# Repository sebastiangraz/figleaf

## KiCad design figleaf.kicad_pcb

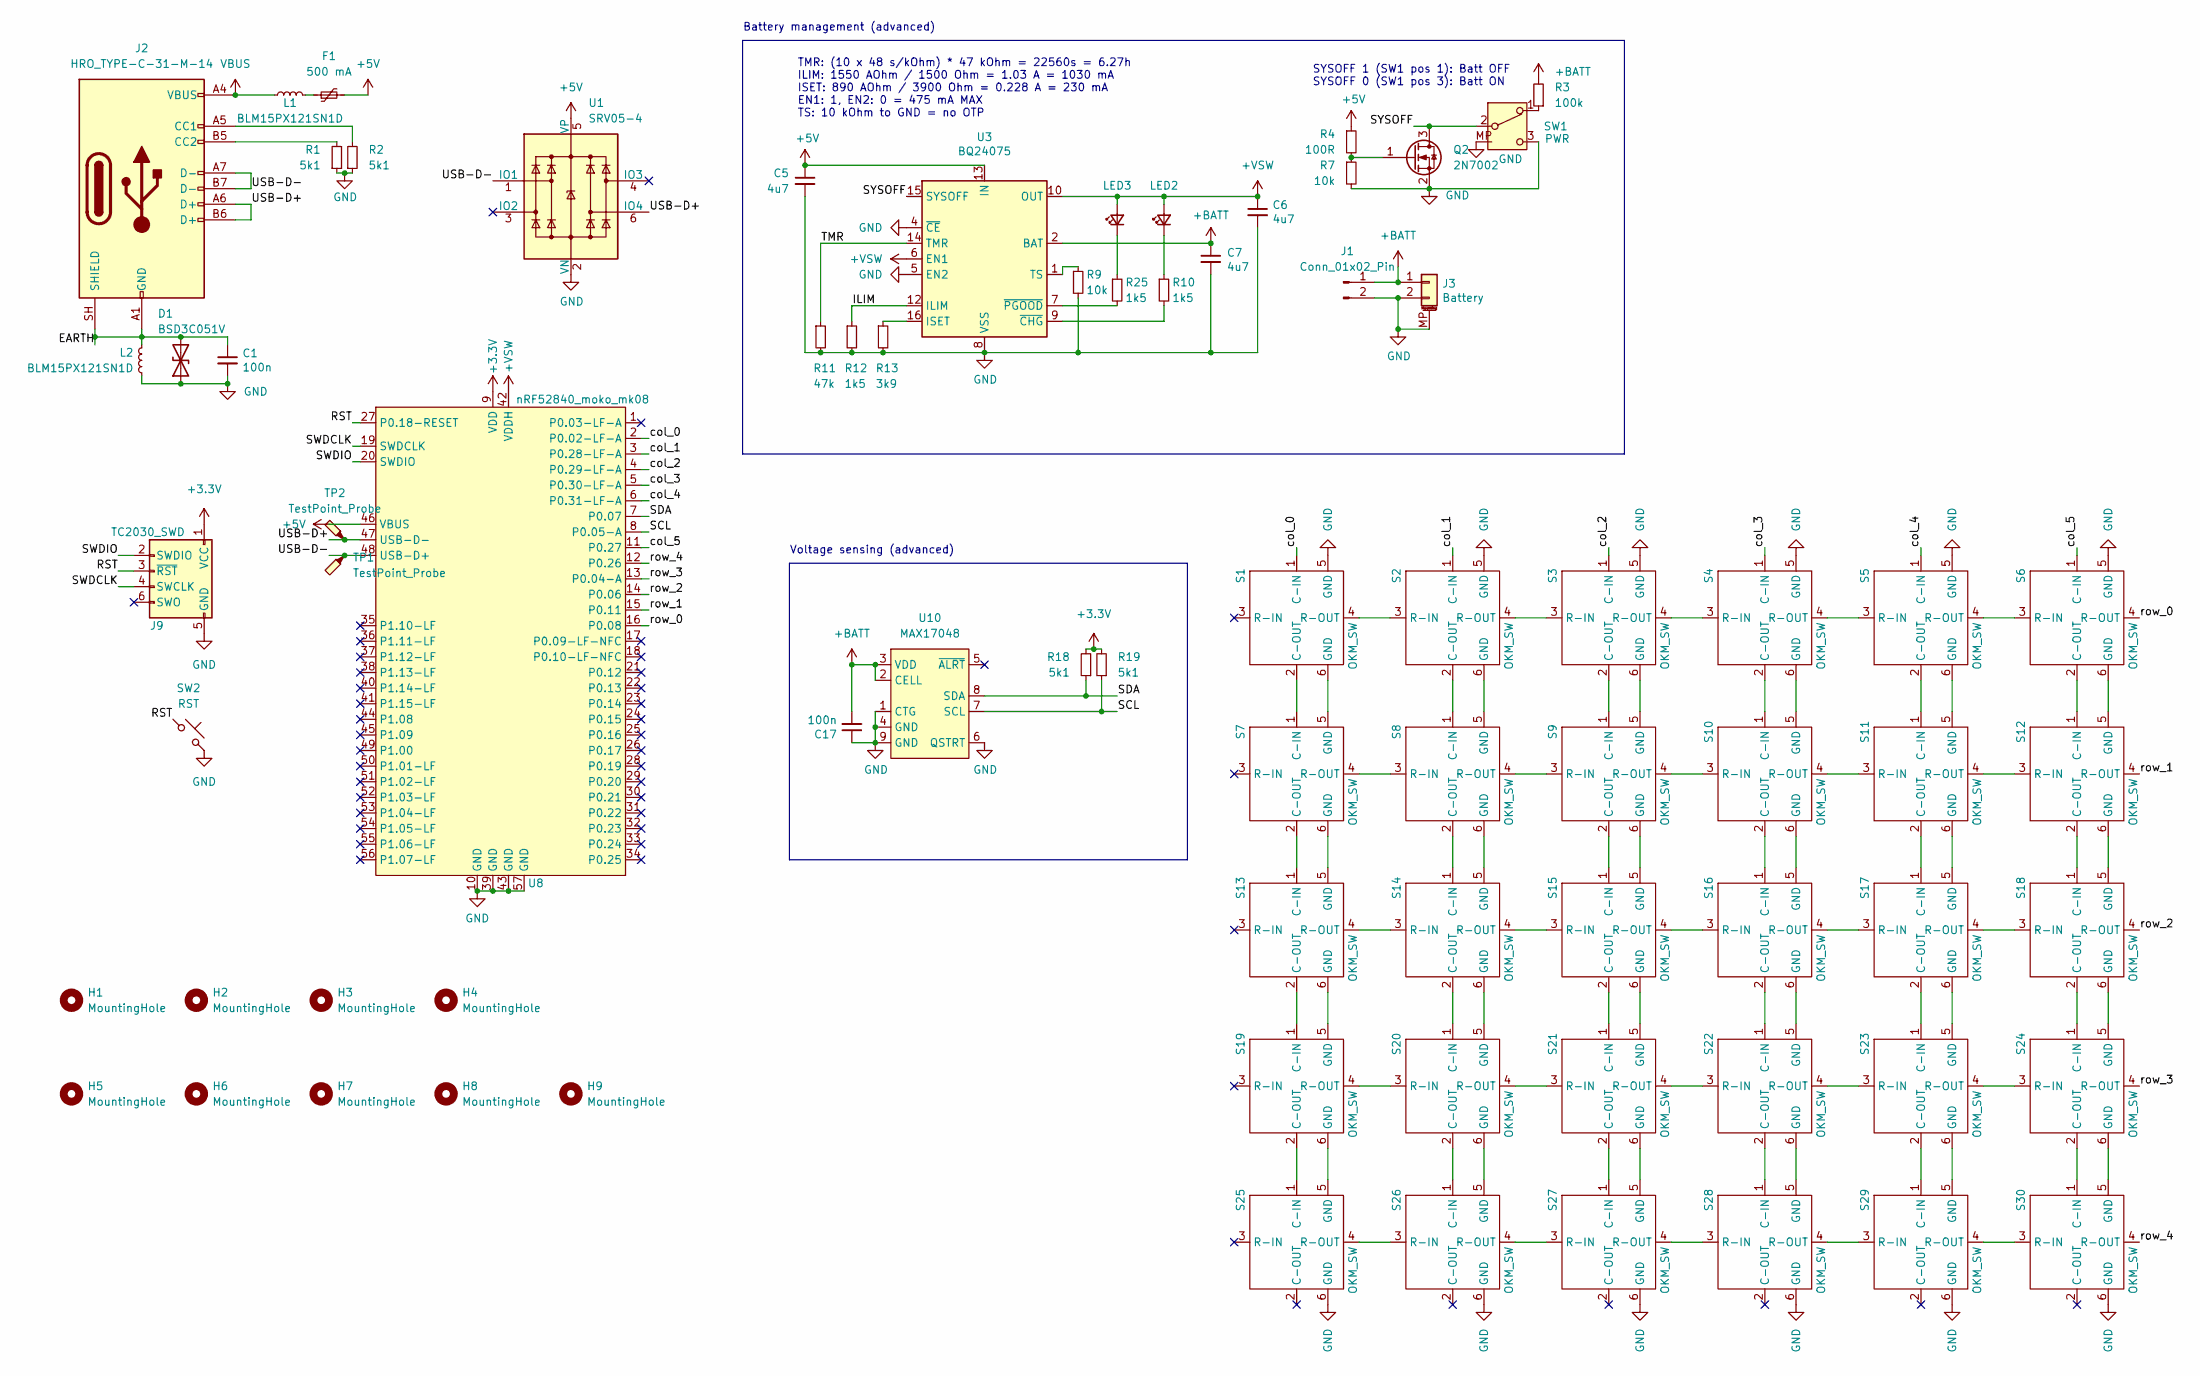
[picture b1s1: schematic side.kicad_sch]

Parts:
C1, C17: 100n; C_0402_1005Metric
C5, C6, C7: 4u7; C_0402_1005Metric
D1: BSD3C051V; D_SOD-323
F1: 500 mA; Fuse_1206_3216Metric
H1, H2, H3, H4, H5, H6, H7, H8, H9: MountingHole; MHOLE_M2
J1: Conn_01x02_Pin; BATT_CONN_SMD
J2: HRO_TYPE-C-31-M-14; USB_C_Receptacle_HRO_TYPE-C-31-M-14
J3: Battery; JST_SH_SM02B-SRSS-TB_1x02-1MP_P1.00mm_Horizontal; LCSC C505023
J9: TC2030_SWD; CON_TC2030_outlined
L1, L2: BLM15PX121SN1D; L_0402_1005Metric
LED2: LW QH8G-Q2OO-3K5L-1; LED_0402_1005Metric
LED3: LT VH9G-Q2OO-25-1; LED_0402_1005Metric
Q2: 2N7002; SOT-23
R1, R2, R18, R19: 5k1; R_0402_1005Metric
R3: 100k; R_0402_1005Metric
R4: 100R; R_0402_1005Metric
R7, R9: 10k; R_0402_1005Metric
R10, R12, R25: 1k5; R_0402_1005Metric
R11: 47k; R_0402_1005Metric
R13: 3k9; R_0402_1005Metric
S1, S2, S3, S4, S5, S6, S7, S8, S9, S10, S11, S12, S13, S14, S15, S16, S17, S18, S19, S20, S21, S22, S23, S24, S25, S26, S27, S28, S29, S30: OKM_SW
SW1: PWR; ALPS_SPDT_SW
SW2: RST; SW_SPST_B3U-3000P-B
TP1, TP2: TestPoint_Probe; TestPoint_Pad_D1.0mm
U1: SRV05-4; SOT-23-6
U3: BQ24075; VQFN-16-1EP_3x3mm_P0.5mm_EP1.6x1.6mm
U8: nRF52840_moko_mk08; MOKO_MK08
U10: MAX17048; DFN-8-1EP_2x2mm_P0.5mm_EP0.7x1.3mm_SM0.22mm

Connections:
+3.3V: J9.1 (VCC), R18.2, R19.2, U8.9 (VDD); also elsewhere on the board
+5V: C5.1, F1.2, R4.1, U1.5 (VP), U3.13 (IN), U8.46 (VBUS); also elsewhere on the board
+BATT: C7.1, C17.2, J1.1, J3.1, R3.2, U3.2 (BAT), U3.3 (BAT), U10.2 (CELL), U10.3 (VDD); also elsewhere on the board
+VSW: C6.1, LED2.2 (A), LED3.2 (A), U3.6 (EN1), U3.10 (OUT), U3.11 (OUT), U8.42 (VDDH); also elsewhere on the board
/left/EARTH: C1.1, D1.2 (A2), J2.A1 (GND), J2.A12 (GND), J2.B1 (GND), J2.B12 (GND), J2.SH (SHIELD), L2.1
/left/ILIM: R12.1, U3.12 (ILIM)
/left/RST: J9.3 (~RST), SW2.1, U8.27 (P0.18-RESET)
/left/SCL: R19.1, U8.8 (P0.05-A), U10.7 (SCL)
/left/SDA: R18.1, U8.7 (P0.07), U10.8 (SDA)
/left/SWDCLK: J9.4 (SWCLK), U8.19 (SWDCLK)
/left/SWDIO: J9.2 (SWDIO), U8.20 (SWDIO)
/left/SYSOFF: Q2.3 (D), SW1.2 (B), U3.15 (SYSOFF)
/left/TMR: R11.1, U3.14 (TMR)
/left/USB-D+: J2.A6 (D+), J2.B6 (D+), TP2.1 (1_1), U1.6 (IO4), U8.47 (USB-D-)
/left/USB-D-: J2.A7 (D-), J2.B7 (D-), TP1.1 (1_1), U1.1 (IO1), U8.48 (USB-D+)
/left/col_0: S1.1 (C-IN), U8.2 (P0.02-LF-A)
/left/col_1: S2.1 (C-IN), U8.3 (P0.28-LF-A)
/left/col_2: S3.1 (C-IN), U8.4 (P0.29-LF-A)
/left/col_3: S4.1 (C-IN), U8.5 (P0.30-LF-A)
/left/col_4: S5.1 (C-IN), U8.6 (P0.31-LF-A)
/left/col_5: S6.1 (C-IN), U8.11 (P0.27)
/left/row_0: S6.4 (R-OUT), U8.16 (P0.08)
/left/row_1: S12.4 (R-OUT), U8.15 (P0.11)
/left/row_2: S18.4 (R-OUT), U8.14 (P0.06)
/left/row_3: S24.4 (R-OUT), U8.13 (P0.04-A)
/left/row_4: S30.4 (R-OUT), U8.12 (P0.26)
GND: C1.2, C5.2, C6.2, C7.2, C17.1, D1.1 (A1), J1.2, J3.2, J3.MP (MountPin), J9.5 (GND), L2.2, Q2.2 (S), R1.1, R2.1, R7.2, R9.2, R11.2, R12.2, R13.2, S1.5 (GND), S2.5 (GND), S3.5 (GND), S4.5 (GND), S5.5 (GND), S6.5 (GND), S25.6 (GND), S26.6 (GND), S27.6 (GND), S28.6 (GND), S29.6 (GND), S30.6 (GND), SW1.3 (C), SW1.MP, SW2.2, U1.2 (VN), U3.4 (~CE), U3.5 (EN2), U3.8 (VSS), U3.17 (VSS), U8.10 (GND), U8.39 (GND), U8.43 (GND), U8.57 (GND), U10.1 (CTG), U10.4 (GND), U10.6 (QSTRT), U10.9 (GND); also elsewhere on the board
unnamed: F1.1, L1.2
unnamed: J2.A5 (CC1), R2.2
unnamed: J2.B5 (CC2), R1.2
unnamed: LED2.1 (K), R10.1
unnamed: LED3.1 (K), R25.1
unnamed: Q2.1 (G), R4.2, R7.1
unnamed: S1.2 (C-OUT), S7.1 (C-IN)
unnamed: S1.6 (GND), S7.5 (GND)
unnamed: S1.4 (R-OUT), S2.3 (R-IN)
unnamed: S2.2 (C-OUT), S8.1 (C-IN)
unnamed: S2.6 (GND), S8.5 (GND)
unnamed: S2.4 (R-OUT), S3.3 (R-IN)
unnamed: S3.2 (C-OUT), S9.1 (C-IN)
unnamed: S3.6 (GND), S9.5 (GND)
unnamed: S3.4 (R-OUT), S4.3 (R-IN)
unnamed: S4.4 (R-OUT), S5.3 (R-IN)
unnamed: S5.4 (R-OUT), S6.3 (R-IN)
unnamed: S7.4 (R-OUT), S8.3 (R-IN)
unnamed: S8.4 (R-OUT), S9.3 (R-IN)
unnamed: S4.2 (C-OUT), S10.1 (C-IN)
unnamed: S10.2 (C-OUT), S16.1 (C-IN)
unnamed: S4.6 (GND), S10.5 (GND)
unnamed: S10.6 (GND), S16.5 (GND)
unnamed: S9.4 (R-OUT), S10.3 (R-IN)
unnamed: S10.4 (R-OUT), S11.3 (R-IN)
unnamed: S5.2 (C-OUT), S11.1 (C-IN)
unnamed: S11.2 (C-OUT), S17.1 (C-IN)
unnamed: S5.6 (GND), S11.5 (GND)
unnamed: S11.6 (GND), S17.5 (GND)
unnamed: S11.4 (R-OUT), S12.3 (R-IN)
unnamed: S6.2 (C-OUT), S12.1 (C-IN)
unnamed: S12.2 (C-OUT), S18.1 (C-IN)
unnamed: S6.6 (GND), S12.5 (GND)
unnamed: S12.6 (GND), S18.5 (GND)
unnamed: S7.2 (C-OUT), S13.1 (C-IN)
unnamed: S13.2 (C-OUT), S19.1 (C-IN)
unnamed: S7.6 (GND), S13.5 (GND)
unnamed: S13.6 (GND), S19.5 (GND)
unnamed: S13.4 (R-OUT), S14.3 (R-IN)
unnamed: S8.2 (C-OUT), S14.1 (C-IN)
unnamed: S14.2 (C-OUT), S20.1 (C-IN)
unnamed: S8.6 (GND), S14.5 (GND)
unnamed: S14.6 (GND), S20.5 (GND)
unnamed: S14.4 (R-OUT), S15.3 (R-IN)
unnamed: S9.2 (C-OUT), S15.1 (C-IN)
unnamed: S15.2 (C-OUT), S21.1 (C-IN)
unnamed: S9.6 (GND), S15.5 (GND)
unnamed: S15.6 (GND), S21.5 (GND)
unnamed: S15.4 (R-OUT), S16.3 (R-IN)
unnamed: S16.2 (C-OUT), S22.1 (C-IN)
unnamed: S16.6 (GND), S22.5 (GND)
unnamed: S16.4 (R-OUT), S17.3 (R-IN)
unnamed: S17.2 (C-OUT), S23.1 (C-IN)
unnamed: S17.6 (GND), S23.5 (GND)
unnamed: S17.4 (R-OUT), S18.3 (R-IN)
unnamed: S18.2 (C-OUT), S24.1 (C-IN)
unnamed: S18.6 (GND), S24.5 (GND)
unnamed: S19.2 (C-OUT), S25.1 (C-IN)
unnamed: S19.6 (GND), S25.5 (GND)
unnamed: S19.4 (R-OUT), S20.3 (R-IN)
unnamed: S20.2 (C-OUT), S26.1 (C-IN)
unnamed: S20.6 (GND), S26.5 (GND)
unnamed: S20.4 (R-OUT), S21.3 (R-IN)
unnamed: S21.2 (C-OUT), S27.1 (C-IN)
unnamed: S21.6 (GND), S27.5 (GND)
unnamed: S21.4 (R-OUT), S22.3 (R-IN)
unnamed: S22.2 (C-OUT), S28.1 (C-IN)
unnamed: S22.6 (GND), S28.5 (GND)
unnamed: S22.4 (R-OUT), S23.3 (R-IN)
unnamed: S23.2 (C-OUT), S29.1 (C-IN)
unnamed: S23.6 (GND), S29.5 (GND)
unnamed: S23.4 (R-OUT), S24.3 (R-IN)
unnamed: S24.2 (C-OUT), S30.1 (C-IN)
unnamed: S24.6 (GND), S30.5 (GND)
unnamed: S25.4 (R-OUT), S26.3 (R-IN)
unnamed: S26.4 (R-OUT), S27.3 (R-IN)
unnamed: S27.4 (R-OUT), S28.3 (R-IN)
unnamed: S28.4 (R-OUT), S29.3 (R-IN)
unnamed: S29.4 (R-OUT), S30.3 (R-IN)
unnamed: R3.1, SW1.1 (A)
unnamed: R13.1, U3.16 (ISET)
unnamed: R9.1, U3.1 (TS)
unnamed: R10.2, U3.9 (~CHG)
unnamed: R25.2, U3.7 (~PGOOD)
VBUS: J2.A4 (VBUS), J2.A9 (VBUS), J2.B4 (VBUS), J2.B9 (VBUS), L1.1; also elsewhere on the board

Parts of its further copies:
C2, C3, C4: 4u7; C_0402_1005Metric
C8, C9: 100n; C_0402_1005Metric
D2: BSD3C051V; D_SOD-323
F2: 500 mA; Fuse_1206_3216Metric
H10, H11, H12, H13, H14, H15, H16, H17, H18: MountingHole; MHOLE_M2
J4: HRO_TYPE-C-31-M-14; USB_C_Receptacle_HRO_TYPE-C-31-M-14
J5: Conn_01x02_Pin; BATT_CONN_SMD
J6: Battery; JST_SH_SM02B-SRSS-TB_1x02-1MP_P1.00mm_Horizontal; LCSC C505023
J7: TC2030_SWD; CON_TC2030_outlined
L3, L4: BLM15PX121SN1D; L_0402_1005Metric
LED1: LW QH8G-Q2OO-3K5L-1; LED_0402_1005Metric
LED4: LT VH9G-Q2OO-25-1; LED_0402_1005Metric
Q1: 2N7002; SOT-23
R5: 100k; R_0402_1005Metric
R6: 100R; R_0402_1005Metric
R8, R14, R23, R24: 5k1; R_0402_1005Metric
R15, R16: 10k; R_0402_1005Metric
R17, R21, R26: 1k5; R_0402_1005Metric
R20: 47k; R_0402_1005Metric
R22: 3k9; R_0402_1005Metric
S31, S32, S33, S34, S35, S36, S37, S38, S39, S40, S41, S42, S43, S44, S45, S46, S47, S48, S49, S50, S51, S52, S53, S54, S55, S56, S57, S58, S59, S60: OKM_SW
SW3: PWR; ALPS_SPDT_SW
SW4: RST; SW_SPST_B3U-3000P-B
TP3, TP4: TestPoint_Probe; TestPoint_Pad_D1.0mm
U2: SRV05-4; SOT-23-6
U4: BQ24075; VQFN-16-1EP_3x3mm_P0.5mm_EP1.6x1.6mm
U5: nRF52840_moko_mk08; MOKO_MK08
U6: MAX17048; DFN-8-1EP_2x2mm_P0.5mm_EP0.7x1.3mm_SM0.22mm

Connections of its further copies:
+3.3V: J7.1 (VCC), R23.2, R24.2, U5.9 (VDD); also elsewhere on the board
+5V: C2.1, F2.2, R6.1, U2.5 (VP), U4.13 (IN), U5.46 (VBUS); also elsewhere on the board
+BATT: C4.1, C9.2, J5.1, J6.1, R5.2, U4.2 (BAT), U4.3 (BAT), U6.2 (CELL), U6.3 (VDD); also elsewhere on the board
+VSW: C3.1, LED1.2 (A), LED4.2 (A), U4.6 (EN1), U4.10 (OUT), U4.11 (OUT), U5.42 (VDDH); also elsewhere on the board
/right/EARTH: C8.1, D2.2 (A2), J4.A1 (GND), J4.A12 (GND), J4.B1 (GND), J4.B12 (GND), J4.SH (SHIELD), L4.1
/right/ILIM: R21.1, U4.12 (ILIM)
/right/RST: J7.3 (~RST), SW4.1, U5.27 (P0.18-RESET)
/right/SCL: R24.1, U5.8 (P0.05-A), U6.7 (SCL)
/right/SDA: R23.1, U5.7 (P0.07), U6.8 (SDA)
/right/SWDCLK: J7.4 (SWCLK), U5.19 (SWDCLK)
/right/SWDIO: J7.2 (SWDIO), U5.20 (SWDIO)
/right/SYSOFF: Q1.3 (D), SW3.2 (B), U4.15 (SYSOFF)
/right/TMR: R20.1, U4.14 (TMR)
/right/USB-D+: J4.A6 (D+), J4.B6 (D+), TP3.1 (1_1), U2.6 (IO4), U5.47 (USB-D-)
/right/USB-D-: J4.A7 (D-), J4.B7 (D-), TP4.1 (1_1), U2.1 (IO1), U5.48 (USB-D+)
/right/col_0: S31.1 (C-IN), U5.2 (P0.02-LF-A)
/right/col_1: S32.1 (C-IN), U5.3 (P0.28-LF-A)
/right/col_2: S33.1 (C-IN), U5.4 (P0.29-LF-A)
/right/col_3: S34.1 (C-IN), U5.5 (P0.30-LF-A)
/right/col_4: S35.1 (C-IN), U5.6 (P0.31-LF-A)
/right/col_5: S36.1 (C-IN), U5.11 (P0.27)
/right/row_0: S36.4 (R-OUT), U5.16 (P0.08)
/right/row_1: S42.4 (R-OUT), U5.15 (P0.11)
/right/row_2: S48.4 (R-OUT), U5.14 (P0.06)
/right/row_3: S54.4 (R-OUT), U5.13 (P0.04-A)
/right/row_4: S60.4 (R-OUT), U5.12 (P0.26)
GND: C2.2, C3.2, C4.2, C8.2, C9.1, D2.1 (A1), J5.2, J6.2, J6.MP (MountPin), J7.5 (GND), L4.2, Q1.2 (S), R8.1, R14.1, R15.2, R16.2, R20.2, R21.2, R22.2, S31.5 (GND), S32.5 (GND), S33.5 (GND), S34.5 (GND), S35.5 (GND), S36.5 (GND), S55.6 (GND), S56.6 (GND), S57.6 (GND), S58.6 (GND), S59.6 (GND), S60.6 (GND), SW3.3 (C), SW3.MP, SW4.2, U2.2 (VN), U4.4 (~CE), U4.5 (EN2), U4.8 (VSS), U4.17 (VSS), U5.10 (GND), U5.39 (GND), U5.43 (GND), U5.57 (GND), U6.1 (CTG), U6.4 (GND), U6.6 (QSTRT), U6.9 (GND); also elsewhere on the board
unnamed: F2.1, L3.2
unnamed: J4.A5 (CC1), R14.2
unnamed: J4.B5 (CC2), R8.2
unnamed: LED1.1 (K), R17.1
unnamed: LED4.1 (K), R26.1
unnamed: Q1.1 (G), R6.2, R15.1
unnamed: S31.2 (C-OUT), S37.1 (C-IN)
unnamed: S31.6 (GND), S37.5 (GND)
unnamed: S31.4 (R-OUT), S32.3 (R-IN)
unnamed: S32.2 (C-OUT), S38.1 (C-IN)
unnamed: S32.6 (GND), S38.5 (GND)
unnamed: S32.4 (R-OUT), S33.3 (R-IN)
unnamed: S33.2 (C-OUT), S39.1 (C-IN)
unnamed: S33.6 (GND), S39.5 (GND)
unnamed: S33.4 (R-OUT), S34.3 (R-IN)
unnamed: S34.2 (C-OUT), S40.1 (C-IN)
unnamed: S34.6 (GND), S40.5 (GND)
unnamed: S34.4 (R-OUT), S35.3 (R-IN)
unnamed: S35.2 (C-OUT), S41.1 (C-IN)
unnamed: S35.6 (GND), S41.5 (GND)
unnamed: S35.4 (R-OUT), S36.3 (R-IN)
unnamed: S36.2 (C-OUT), S42.1 (C-IN)
unnamed: S36.6 (GND), S42.5 (GND)
unnamed: S37.2 (C-OUT), S43.1 (C-IN)
unnamed: S37.6 (GND), S43.5 (GND)
unnamed: S37.4 (R-OUT), S38.3 (R-IN)
unnamed: S38.2 (C-OUT), S44.1 (C-IN)
unnamed: S38.6 (GND), S44.5 (GND)
unnamed: S38.4 (R-OUT), S39.3 (R-IN)
unnamed: S39.2 (C-OUT), S45.1 (C-IN)
unnamed: S39.6 (GND), S45.5 (GND)
unnamed: S39.4 (R-OUT), S40.3 (R-IN)
unnamed: S40.2 (C-OUT), S46.1 (C-IN)
unnamed: S40.6 (GND), S46.5 (GND)
unnamed: S40.4 (R-OUT), S41.3 (R-IN)
unnamed: S41.2 (C-OUT), S47.1 (C-IN)
unnamed: S41.6 (GND), S47.5 (GND)
unnamed: S41.4 (R-OUT), S42.3 (R-IN)
unnamed: S42.2 (C-OUT), S48.1 (C-IN)
unnamed: S42.6 (GND), S48.5 (GND)
unnamed: S43.2 (C-OUT), S49.1 (C-IN)
unnamed: S43.6 (GND), S49.5 (GND)
unnamed: S43.4 (R-OUT), S44.3 (R-IN)
unnamed: S44.2 (C-OUT), S50.1 (C-IN)
unnamed: S44.6 (GND), S50.5 (GND)
unnamed: S44.4 (R-OUT), S45.3 (R-IN)
unnamed: S45.2 (C-OUT), S51.1 (C-IN)
unnamed: S45.6 (GND), S51.5 (GND)
unnamed: S45.4 (R-OUT), S46.3 (R-IN)
unnamed: S46.2 (C-OUT), S52.1 (C-IN)
unnamed: S46.6 (GND), S52.5 (GND)
unnamed: S46.4 (R-OUT), S47.3 (R-IN)
unnamed: S47.2 (C-OUT), S53.1 (C-IN)
unnamed: S47.6 (GND), S53.5 (GND)
unnamed: S47.4 (R-OUT), S48.3 (R-IN)
unnamed: S48.2 (C-OUT), S54.1 (C-IN)
unnamed: S48.6 (GND), S54.5 (GND)
unnamed: S49.2 (C-OUT), S55.1 (C-IN)
unnamed: S49.6 (GND), S55.5 (GND)
unnamed: S49.4 (R-OUT), S50.3 (R-IN)
unnamed: S50.2 (C-OUT), S56.1 (C-IN)
unnamed: S50.6 (GND), S56.5 (GND)
unnamed: S50.4 (R-OUT), S51.3 (R-IN)
unnamed: S51.2 (C-OUT), S57.1 (C-IN)
unnamed: S51.6 (GND), S57.5 (GND)
unnamed: S51.4 (R-OUT), S52.3 (R-IN)
unnamed: S52.2 (C-OUT), S58.1 (C-IN)
unnamed: S52.6 (GND), S58.5 (GND)
unnamed: S52.4 (R-OUT), S53.3 (R-IN)
unnamed: S53.2 (C-OUT), S59.1 (C-IN)
unnamed: S53.6 (GND), S59.5 (GND)
unnamed: S53.4 (R-OUT), S54.3 (R-IN)
unnamed: S54.2 (C-OUT), S60.1 (C-IN)
unnamed: S54.6 (GND), S60.5 (GND)
unnamed: S55.4 (R-OUT), S56.3 (R-IN)
unnamed: S56.4 (R-OUT), S57.3 (R-IN)
unnamed: S57.4 (R-OUT), S58.3 (R-IN)
unnamed: S58.4 (R-OUT), S59.3 (R-IN)
unnamed: S59.4 (R-OUT), S60.3 (R-IN)
unnamed: R5.1, SW3.1 (A)
unnamed: R22.1, U4.16 (ISET)
unnamed: R16.1, U4.1 (TS)
unnamed: R17.2, U4.9 (~CHG)
unnamed: R26.2, U4.7 (~PGOOD)
VBUS: J4.A4 (VBUS), J4.A9 (VBUS), J4.B4 (VBUS), J4.B9 (VBUS), L3.1; also elsewhere on the board

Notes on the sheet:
SYSOFF 1 (SW1 pos 1): Batt OFF SYSOFF 0 (SW1 pos 3): Batt ON
TMR: (10 x 48 s/kOhm) * 47 kOhm = 22560s = 6.27h ILIM: 1550 AOhm / 1500 Ohm = 1.03 A = 1030 mA ISET: 890 AOhm / 3900 Ohm = 0.228 A = 230 mA EN1: 1, EN2: 0 = 475 mA MAX TS: 10 kOhm to GND = no OTP
Voltage sensing (advanced)
Battery management (advanced)

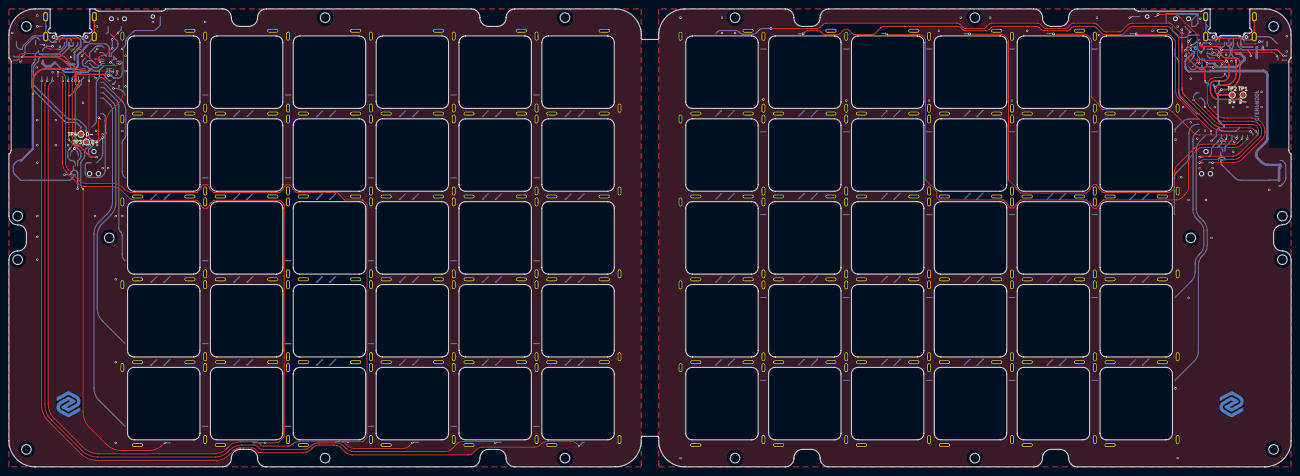
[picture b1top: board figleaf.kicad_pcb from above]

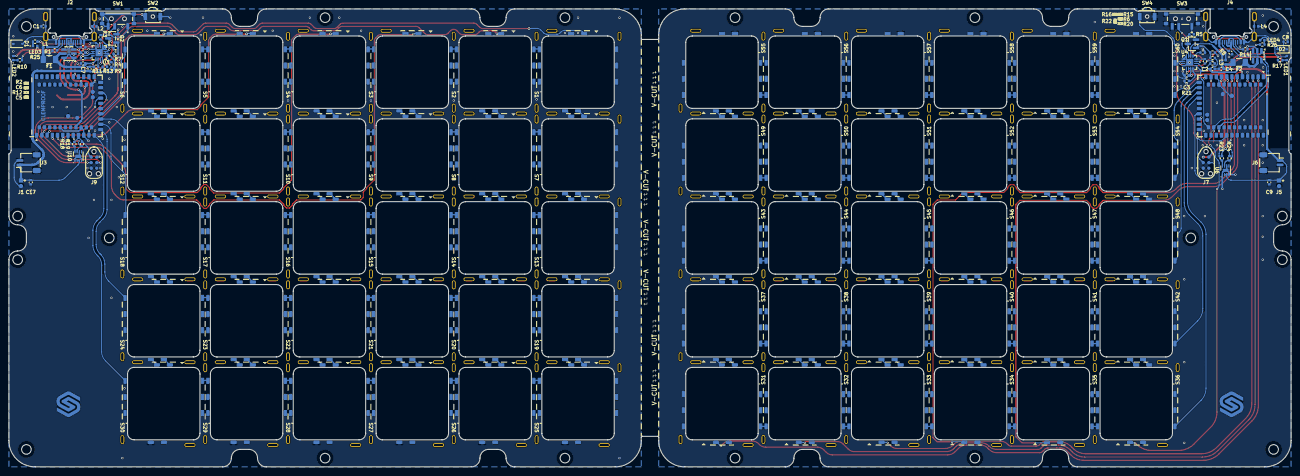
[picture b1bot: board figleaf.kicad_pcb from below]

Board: 2 copper layers, 294.0 x 105.0 mm, 152 parts (68 on the bottom side), 218 nets.

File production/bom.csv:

Designator,Footprint,Quantity,Value,LCSC Part #
"C1, C17",0402,2,100n,
"C5, C6, C7",0402,3,4u7,
D1,D_SOD-323,1,BSD3C051V,
F1,1206,1,500 mA,
J1,Generic_Battery_Connector,1,Conn_01x02_Pin,
J2,USB_C_Receptacle_HRO_TYPE-C-31-M-14,1,HRO_TYPE-C-31-M-14,
J3,JST_SH_SM02B-SRSS-TB_1x02-1MP_P1.00mm_Horizontal,1,Battery,C505023
J9,CON_TC2030_outlined,1,TC2030_SWD,
"L1, L2",0402,2,BLM15PX121SN1D,
LED2,0402,1,orange,
Q2,SOT-23,1,2N7002,
"R1, R18, R19, R2",0402,4,5k1,
"R10, R12",0402,2,1k5,
R11,0402,1,47k,
R13,0402,1,3k9,
R3,0402,1,100k,
R4,0402,1,100R,
"R7, R9",0402,2,10k,
"S1, S10, S11, S12, S13, S14, S15, S16, S17, S18, S19, S2, S20, S21, S22, S23, S24, S25, S26, S27, S28, S29, S3, S30, S4, S5, S6, S7, S8, S9",One Key Module Graz,30,SW_OKM,
SW1,SW_SSSS811101,1,PWR,
SW2,SW_SPST_B3U-3000P-B,1,RST,
U1,SOT-23-6,1,SRV05-4,
U10,DFN-8-1EP_2x2mm_P0.5mm_EP0.7x1.3mm,1,MAX17048,
U3,VQFN-16-1EP_3x3mm_P0.5mm_EP1.6x1.6mm,1,BQ24075,
U8,nRF52840_moko_mk08_GRAZ,1,nRF52840_moko_mk08,

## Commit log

2026-01-23 setup
2026-01-23 add assets
2026-01-23 add mcu
2026-01-23 add schematic and pinouts for mcu
2026-01-23 testing llmd mcu
2026-02-01 Add new assets
2026-02-01 Add proper MCU symbol
2026-02-01 progress on 2x2 test schematics
2026-02-02 kicad progress
2026-02-02 progress pcb
2026-02-02 add all switches to pcb
2026-02-02 progress
2026-02-03 PCB progress, switches to 19x19 pitch
2026-02-03 Add SW ground conn
2026-02-03 Add teardrops
2026-02-05 swap to my OKM footprint + updated TH pads for switch lugs
2026-02-05 fix all DRC issues
2026-02-05 Add n!n SMD variant
2026-02-05 PCB cleanup
2026-02-05 Add power components v1
2026-02-05 mcu silkscreen +B sign fix
2026-02-06 testing gerber file
2026-02-09 backup before sharing progress
2026-02-09 Add sidemounted reset
2026-02-09 DRC silkscreen fix
2026-02-09 move vias from back MCU to avoid silkscreen + add power labels
2026-02-09 adjust label
2026-02-09 add more mounting holes
2026-02-09 testing new fill type
2026-02-09 move Bcu layer to a better place
2026-02-09 Adjust fr4 thickness
2026-02-09 update pcb step
2026-02-10 add step PCB assets
2026-02-11 git cleanup
2026-02-11 start with seeed mcu
2026-02-11 new xiao MCU progress
2026-02-11 PCB progress
2026-02-11 larger mcu pads + move MCU away from mounting hole
2026-02-11 fix DRC with new setup
2026-02-11 move MCU into narrower spot
2026-02-11 move edge cuts to narrow setup
2026-02-12 checkpoint
2026-02-15 checkpoint before comp flip
2026-02-15 flip progress 1
2026-02-15 flip progress 2
2026-02-15 flipping completed
2026-02-15 flipping completed fr
2026-02-15 Add new step pcb
2026-02-17 V1 integration
2026-02-17 add step
2026-02-17 flip usb-c
2026-02-17 add ignore
2026-02-18 progress + add jst conn
2026-02-18 Add matrix
2026-02-19 tracing progress
2026-02-19 prog
2026-02-19 remove J4 connector, not using DB board
2026-02-19 finish routing v1
2026-02-19 pre silkscreen checkpoint
2026-02-19 Fix silkscreen + DRC
2026-02-20 Good overall V1 checkpoint
2026-02-20 Adjustment PCB
2026-02-20 remove vias from smd pads
2026-02-20 remove vias from smd pads 2
2026-02-20 remove vias from smd pads 3
2026-02-20 remove vias from smd pads 4
2026-02-22 vsw F.cu thickness + move via
2026-02-22 move usb outwards + add mounting holes + fillet
2026-02-22 progress on mounting hole + moving usb
2026-02-22 DRC fixws
2026-02-22 move silkscreen
2026-02-22 find device center
2026-02-22 add mt hole
2026-02-22 remove old vias
2026-02-23 remove mt hole
2026-02-27 move pcb magnet edge cuts
2026-02-28 move jst + add optional battery pad
2026-02-28 sch fix
2026-02-28 update battery conn silkscreen
2026-02-28 reorder & update mt holes count
2026-02-28 move vias from col pads
2026-03-01 add on off silkscreen pwr
2026-03-01 move batt conn
2026-03-03 move pwr and rst SW
2026-03-04 new step
2026-03-05 move +B conn
2026-03-05 Fix DRC
2026-03-05 cleanup
2026-03-05 move RST
2026-03-09 move MCU inwards
2026-03-10 Move LED near antenna
2026-03-10 small deets
2026-03-10 update OKM footprint, larger GND, smaller RADI
2026-03-10 Adding new magnet through holes
2026-03-10 move mounting magnet holes (moles?)
2026-03-10 move moles 0.05mm lol
2026-03-10 do it agane
2026-03-11 pwr sym
2026-03-11 rm pre_revert files
2026-03-11 update OKM footprint
2026-03-11 update to polyfuse & move silkscreens
2026-03-11 DRC fixes
2026-03-12 Add alps pwr sw
2026-03-12 update switch model
2026-03-17 Add thin bezel test + move front IO checkpoint
2026-03-17 adjust IOs
2026-03-17 change pour clearance
2026-03-17 change pour clearance saved
2026-03-17 pcb progress refactor
2026-03-18 all routed
2026-03-18 add logo
2026-03-18 stackup colors
2026-03-18 smol tweaks
2026-03-18 rounded bosses
2026-03-18 drc edges
2026-03-21 Move PWR RST, fix SW Silkscreen
2026-03-21 cleanup + pre-rename
2026-03-21 rename complete + cleanup + gitignore fixes
2026-03-21 data line thickness + mounting cuts
2026-03-21 trace thickness saved
2026-03-21 new bosses
2026-03-21 boss radius 1.5mm aye
2026-03-21 IO indent
2026-03-21 move traces from screw bosses
2026-03-21 DRC and ground plane fixes
2026-03-21 Make alt batt con smd only
2026-03-22 mt holes larger keepout area for counterdrilling
2026-03-23 Create better cutouts MCU
2026-03-23 Create better cutouts MCU saved
2026-03-23 Move MCU inwards, for the last time pls bro
2026-03-23 Move XY to better coord
2026-03-23 adjust mcu cutout
2026-03-23 move vias
2026-03-23 testing m2 mounting holes
2026-03-23 finish m2 refactor
2026-03-26 Version & date + OKM minor fixes
2026-03-26 pre right side
2026-03-26 trace spacing
2026-03-26 pre-right side, the return
2026-03-26 change GND_L to GND
2026-03-26 pre right fr
2026-03-26 add PCB changes
2026-03-26 cache
2026-03-27 add keepout to mounting holes
2026-03-29 update fixture screw pos
2026-03-29 update casetop bosses
2026-03-29 nicer v1 label
2026-04-05 pre split
2026-04-05 v1 progress
2026-04-05 v1 progress pcb
2026-04-06 finish routing PCB
2026-04-06 finish routing PCB + DRC
2026-04-06 finish routing PCB + DRC + save
2026-04-07 OKM cap appearance
2026-04-14 update OKMs
2026-04-14 migration to KiCad 10
2026-04-14 rm .history
2026-04-15 Fillet tracks + arrange layout for PCB v-cut
2026-04-15 GND fill clearance for VCUT
2026-04-15 Add vcut to user.comments as well
2026-04-15 rm cached sch doc
2026-04-15 c1 silk pos
2026-04-15 bom rules
2026-04-15 bom updated pcb
2026-04-15 bom updated pcb drc
2026-04-15 rm aux batt conn from bom
2026-04-15 rm sw conn from bom
2026-04-15 new bom zip
2026-04-15 rm gerbers from root + rm micro vias
2026-04-15 post crash
2026-04-15 add back gitignore
2026-04-15 git ignore files
2026-04-15 add trim to git ignore
2026-04-15 rm trim dir
2026-04-16 drc pcb
2026-04-16 add new LED POWERGOOD v1
2026-04-16 settngs
2026-04-16 update VQFN-16-1EP_3x3mm_P0.5mm_EP1.6x1.6mm footprint
2026-04-16 add assets folder
2026-04-16 fused
2026-05-14 Fillet tracks, add teardrops, adjust testpoints for usb
2026-05-14 adjust silkscreens
2026-05-15 Add new DFN fp with 0.22mm mask bridges for manu compat
2026-05-15 adjust traces
2026-05-15 export gerber
2026-05-17 Update pwr switch symbol
2026-05-17 rm SM between usbc IC pins
2026-05-17 swap max17048 2-3 pins, technically more correct
2026-05-19 new step file

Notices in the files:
parts and their libraries:
License: Apache-2.0
